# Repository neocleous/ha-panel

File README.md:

# HA Panel: design files

This branch, `docs`, holds the design of a Home Assistant touch panel: its custom circuit boards and its 3D-printed
enclosure. The panel's software is on the [`main`](https://github.com/neocleous/ha-panel/tree/main) branch.

## The panel
A free-standing Home Assistant panel. A Raspberry Pi 5 shows a full-screen dashboard on a Waveshare 8-inch DSI
touchscreen (1280 × 800, landscape). Around it:
- two speakers (Dayton Audio DMA45-4), driven by the main board's TAS5756M amplifier;
- two microphones for voice, through a ReSpeaker Lite;
- a presence radar (Hi-Link LD2410C);
- air and light sensors (BME680, VEML6030);
- four touch keys below the screen;
- power from a 20 V USB-C charger.

Home Assistant runs on a separate server; the panel is its display, sensor and voice client.

## State (2026-11-23)
- **The boards:** the main board (rev 3.3), the touch board (rev E), the mic strips (rev 3) and the two paste stencils.
  Their fab files are made.
- **The enclosure: the Fusion model is at version 79 and waits for its print re-check.** Versions 68 and 69 replaced the
  melted and glued joints by screws and two printed clamps. Versions 70 to 79 built the fixes that the audit of version 69
  decided, and added a 17th printed part, the radar's holder.
- **The print files are version 67's.** Until the re-check has run and they are made again, they are out of date for the
  shell, the door, the cap, the grommet and the hood, and they lack the two clamps. After versions 70 to 79 they are out
  of date for every printed part but the cradle of the USB-C inlet board, and they lack the radar's holder as well.
- **Next:** the print re-check and the new print files, then a fit trial printed in PLA, the black ABS set, the boards'
  assembly, the build and bring-up.
- **The first panel (v1)** is built and in use. `main` installs its software.

## Folder map
```
hardware/              the three boards and the paste stencil
  main-board/          rev 3.3: power, amplifier, sockets
  mic-strip/           rev 3: one microphone per strip, two strips per panel
  touch-board/         rev E: the four touch keys
  stencil/             the paste stencils: the main board; the touch board with the mic strips
  notes/               parts lists, DigiKey and JLC notes, Raspberry Pi settings
  rev-c/               the first panel's touch board
enclosure/             the housing
  model-v68/           the scripts that made versions 68 and 69 of the Fusion model from version 67
  model-v70/           the scripts that made versions 70 to 79 from version 69 (the audit's fixes)
  print-files/         the scripts that make the print files from the Fusion model
  HA Panel Final.step  the first panel's enclosure
```

Start with [`hardware/README.md`](hardware/README.md) for the boards and [`enclosure/README.md`](enclosure/README.md)
for the housing.

## Where things are that are not in this repo
- **The enclosure model:** Autodesk Fusion, document "HA Panel v5 - tapered", version 79 (work in progress).
- **The print files:** Bambu Studio projects made from version 67, kept on the Mac in
  `~/Documents/HA_panel_renders/print_files_v67/`. Five parts in them are out of date (see
  [`enclosure/README.md`](enclosure/README.md)).
- **The assembly instructions:** not in the repo yet; their final issue is still to come.

## The software
On [`main`](https://github.com/neocleous/ha-panel/tree/main): the installer, the kiosk set-up and the sensor daemon. The
panel pulls `main` every night.

## History
On 2026-11-19 this branch was cleaned up: earlier board revisions, superseded fab sets, the enclosure's build scripts and
audits, and the design's working notes were removed. The history keeps all of it. The tree as it stood
before: [commit 45a38e4](https://github.com/neocleous/ha-panel/tree/45a38e49d72cf125aab3f4aa91dd065b3bc4f7ee).

## Licence
PolyForm Noncommercial 1.0.0: see [`LICENSE.md`](LICENSE.md).

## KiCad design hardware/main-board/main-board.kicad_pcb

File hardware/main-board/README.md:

# Main board, rev 3.3

The panel's power and audio board. It sits behind the display on a printed carrier.

- It takes 20 V from the USB-C inlet board (Adafruit 5807, a HUSB238 PD sink) and protects it.
- It makes 5 V for the Raspberry Pi 5 and the radar, and 3.3 V for the sensors.
- It drives the two speakers with a TAS5756M amplifier.
- It carries the sockets for the touch board, the radar and the two sensor leads, and the wire pads for the Pi's signals.

**State (2026-11-21):** rev 3.3, fab files issued on 2026-11-21 after the pre-order review. From rev 3.2: PS1's row of
13 pins moved 3.0 toward +v to match Mean Well's side view (its body and box did not move; it is to be checked on the
module when it arrives, see "PS1" below); the touch socket J6 takes +3V3 ahead of F4; the via in one of U100's paste
windows is taken out; every silk line is 0.15 wide. The board has not been built or tested yet.

**Checks (KiCad 9.0.9, 2026-11-21):** schematic 0 errors, 0 warnings (`erc-report.txt`); board 0 errors, 0 open
connections, 0 differences to the schematic, 3 warnings: the footprints of J6, J2 and C6 differ from KiCad's library
copies, on purpose (`drc-report.txt`; C6's + mark is 0.1 smaller to clear L1's outline with the wider silk).

**PS1, to check on arrival:** measure on the module, from the pin row, how far its component side stands (Mean Well's
side view: 5.0, the module board's component face 9 from the case's component side and the pins 4 from that face).
About 5.0: rev 3.3 stands. About 8.3: the pin row belongs where rev 3.2 had it; revert commit `5db1985` and issue the
set again. Anything else: stop and look again before soldering.

## Files
| File | What |
|---|---|
| `main-board.kicad_pro`, `main-board.kicad_pcb`, five `.kicad_sch` | the design, KiCad 9.0.9. Project libraries: `lib/ha_panel.kicad_sym`, `lib/ha_panel.pretty` |
| `main-board-schematic.pdf` | the schematic, 5 pages |
| `main-board-rev3.3-assembly.pdf` | **the assembly drawing**, A3, 4 pages: all 120 part names; all values; the placing list with the maker's part numbers; the test pads, connectors and the back face. Previews of pages 1 and 2: `main-board-rev3.3-assembly-names.png`, `-values.png` |
| [`fab/`](fab/) | **what goes to JLC:** `main-board-rev3.3-jlc-2026-11-21.zip`, the same files unzipped in `gerbers/`, the hole list, the check of the set, and the order sheet; `superseded/` holds the rev 3.2 set, which must not be ordered |
| [`NOTES.md`](NOTES.md) | every value of the circuit with its source; the test pads; the layout |
| [`gpio-leads.md`](gpio-leads.md) | the 13 Pi signal wires: pad, Pi pin, housing, colour |
| `main-board-rev3.2.step`, `main-board-rev3.1-plug-envelopes.step`, [`MAIN_env.md`](MAIN_env.md) | for the enclosure model: the populated board, the plug envelopes, the outline, holes and heights. The STEP file is rev 3.2's: on rev 3.3 only PS1's 13 pin holes sit 3.0 further toward +v, and its pin ends behind the board are in `MAIN_env.md` §5. It was not exported again because this session had no KiCad 3D-model library |
| `main-board-copper-F-B.png` | both outer copper layers (rev 3.3) |
| `main-board-3d-door-side.png`, `main-board-3d-back.png` | renders of the populated board, rev 3.2: on rev 3.3 PS1's pins and its two legends sit 3.0 higher, and the back reads `REV 3.3 2026-11-21` |
| `erc-report.txt`, `drc-report.txt` | KiCad's schematic and board checks |
| [`tools/`](tools/) | scripts that export and check the fab set and the stencil, and draw the assembly drawing |

## How to order
- **Upload** `fab/main-board-rev3.3-jlc-2026-11-21.zip` to JLC as a bare board: no assembly, so no BOM or placement
  file. sha256 `26ff743470ad6834af4412218b2413478ce8ec22a962c775d0f4b1875617acdd`. It replaces the rev 3.2 zip.
- **Options in short:** 4 layers, 87.0 × 57.9 mm, FR-4, 1.6 mm, black with white silkscreen, ENIG, 1 oz outer and
  0.5 oz inner copper, stack-up JLC04161H-7628, vias plugged, outline tolerance ±0.2, "Remove Mark", 5 pieces (1 needed).
  Every option with its reason, and what JLC's review may ask: [`fab/ORDER-SHEET.md`](fab/ORDER-SHEET.md).
- **Paste stencil:** a separate line, 100 × 100 mm, for this board alone: [`../stencil/`](../stencil/).

## Parts
- Every part with its DigiKey line: [`../notes/bom-2026-11-17.md`](../notes/bom-2026-11-17.md), section "Main board
  rev 3.2" (rev 3.3 changed no part). The DigiKey quick-add list is [`../notes/digikey-bom.csv`](../notes/digikey-bom.csv).
- **One 0805 part reads 4.7 µF:** TDK C2012X7R1H475K125AC (50 V). It goes to all five places: C12, C101, C102, C122
  and C123.
- **Not from DigiKey:** LK1, a short piece of 1.0 mm tinned copper wire.

## The board in numbers
- **87.0 × 57.9 × 1.6 mm, 4 layers,** with a relief 1.5 deep in the side edge toward the left speaker (floor over
  v +1.5 … +13.0, inner corners r 1.0). Four 3.2 holes for M3 × 8 screws.
- **Layers:** door side parts and signals · layer 2 ground · layer 3 +5 V, +20 V and the amplifier's supply · back
  signals and ground. Stack-up JLC04161H-7628: copper 0.035 / 0.0152 / 0.0152 / 0.035, prepreg 0.2104, core 1.065.
- **120 names:** 72 surface-mount parts fitted and 9 not fitted, 13 through-hole parts, 3 blocks of wire pads
  (J3, J4, J7), 19 test pads, 4 holes. **Every part is on the door side; nothing is fitted on the back.**
- **Sizes:** nothing smaller than 0603; the finest pitches are U100 (0.5) and U1 (0.65). Connectors are through-hole.
- **Vias:** 243 — 87 of 0.2/0.45, 131 of 0.3/0.6, 25 of 0.4/0.8. Tracks 0.15 and wider. Copper to the edge 0.30;
  the pours 0.50 at the relief.
- **Frame used in every document:** seen from the door, u to the right (toward the left speaker), v up, origin in the
  middle of the board. "From the left edge" is u + 43.5; "from the bottom edge" is v + 28.95.

## Sheets
1. Root — index.
2. **20 V inlet and protection** — J1 (from the USB-C inlet board) → F1 5 A → TPS16630 (under-voltage 17.05 V,
   over-voltage 24.06 V, current limit 3.28 A, soft start 19.6 ms) → +20 V with D1 SMBJ22A.
3. **5 V supply and outputs** — 120 µF – L1 15 µH – 120 µF → NID100-5 (enabled by the protection chip's power-good) →
   22 µF + D2 SMBJ6.0A-E → Pi branch (F2 10 A → wire link LK1 → USB-C socket J2, 10 kΩ on each CC pin) and radar
   branch (F3 1 A). Trim network R8/R9 not fitted.
4. **3.3 V, Pi link, sensors, radar, echo tap** — TPS70933 (enabled by the Pi's 3.3 V) → sensor branch through F4
   (BME680 and VEML6030), the touch socket J6 straight from the regulator (since 2026-11-21) and the amplifier's logic
   rail; 13 wire pads for the Pi's signals (J3, J4); radar (J5) and touch (J6) sockets; one
   4-pin header each for the BME680 (J10) and the VEML6030 (J11); echo tap J7 with six links not fitted.
5. **Amplifier** — TAS5756M stereo, I²C address 0x4C, mute on GPIO22, 10 µH + 0.68 µF output filters, speaker sockets
   J8 (left) and J9 (right).

Every value's source: [`NOTES.md`](NOTES.md) §1 to §4.

## Default fit
| Option | Default | Alternative |
|---|---|---|
| Echo reference | **from USB:** R20–R25 not fitted, J7 empty | from I²S: fit R20–R23 (and R24/R25), other firmware |
| 5 V trim | R8, R9 not fitted (5.0 V) | R8 raises the output; value found on the bench at TP13 |
| Amplifier logic rail | R26 fitted (from the board's 3.3 V) | R27 instead of R26 (from the Pi's 3.3 V) |
| I²S series resistors | R14–R16 0 Ω | 22–47 Ω if the edges ring |
| 5 V module enable | R7 0 Ω (from power-good) | R7 open: the module runs whenever 20 V is there |
| Pi branch | LK1 fitted | LK1 open with a 10 A meter in its place (bench) |

## How to assemble
One pass on the hotplate for every surface-mount part, then the through-hole parts by iron. **Work from
`main-board-rev3.3-assembly.pdf`:** page 1 names, page 2 values, page 3 the placing list, page 4 the back.

**Before you start**
- **Paste:** Sn63/Pb37 no-clean (Chip Quik SMD291AXT4). Check its date.
- **Stencil:** the main board's own stencil, 100 × 100, 0.12 thick.
- **Four parts are moisture-sensitive.** Once its bag is open, each must be soldered within its floor life at 30 °C /
  60 % humidity or less; open the bags on the day. A part whose bag has been open longer is baked per J-STD-033 first.
  - U100 TAS5756M: level 3, 168 hours (TI's package information in the datasheet);
  - U1 TPS16630PWPT: level 2, 1 year (TI);
  - F4 Bel 0ZCJ0020FF2E: level 2a, 4 weeks (Bel, September 2025);
  - F5 Littelfuse 2920L260/33DR: level 2a, 4 weeks (Littelfuse, 2025-02-13).
- **Bare board, meter on ohms:** TP2 (20 V), pad 2 of F5 (amplifier supply), TP9 (5 V) and TP16 (3.3 V) each read open
  to TP7 (ground).

**Order**
1. **Paste** the door side through the stencil.
2. **Place the 72 surface-mount parts,** one line of the placing list at a time.
   - Leave nine places empty: R8, R9, R20 to R25, R27. Their pads get paste like the others.
   - D1 and D2: the band is the cathode and goes to pad 1 (red dot on the drawing).
   - U1, U2, U100: pin 1 at the red dot.
   - F1, F2 and F3 share one body: 5 A, 10 A and 1 A. Read the marking.
3. **Hotplate,** door side up. The back is bare, so the board lies flat. Profile below.
4. **Inspect** U100 and U1 under magnification for bridges and lifted pins, then every other joint.
5. **By iron: 13 through-hole parts,** fitted from the door side and soldered on the back, low to high:
   LK1 (tinned copper wire, 1.0 across) · J2 · J1, J8, J9, J5, J6 · J10, J11 · C7 · C5, C6 · PS1.
   - C5, C6, C7: the + lead in pad 1 (red dot). The stripe on the can marks the − lead.
   - PS1: pin 1 at the end the board marks "+Vo".
   - J2: its pin ends reach only 0.5 behind the board. Solder all 16 contacts and the 4 shell stakes.
   - **Cut the leads of C5, C6, C7 and LK1 to 1.5 or less behind the board.** In the unit the ReSpeaker and the
     display's power lead lie behind the board, and pin ends may stand out 4.0 at most there ([`MAIN_env.md`](MAIN_env.md) §5).
6. **The 13 Pi signal wires** (J3, J4): cut the terminal off the board end, push the wire in **from the back** and
   solder it **on the door side**. Pad by pad: [`gpio-leads.md`](gpio-leads.md). The back prints "PI 1-15" and "PI 35-40".
7. **J7 stays empty.**

**Hotplate profile**
- Follow the paste maker's profile. Chip Quik's chart for SMD291AX (datasheet rev 1.1) runs 25 → 100 → 150 °C, crosses
  the 183 °C melting point and tops at 235 °C, about 240 s in all.
- U100 is rated for 260 °C peak (TI), above that profile.
- U100's thermal pad: the stencil's 2 × 4 windows put 20.16 mm² of paste on it, 72.8 % of the package's nominal
  exposed pad and 61.9 % of the board's 3.70 × 8.80 opening; TI asks for 70 to 80 % (SLAS988B 11.1.3.2). Of the 39
  holes under the pad, 3 lie inside the opening and can take some solder; the other 36 are under soldermask.
- The flux is no-clean: nothing is washed.

**In the unit** (the panel's assembly instructions hold the steps): the display's power lead is plugged onto the
display before the board is screwed on. Plugging order on the board: speakers and 20 V, then touch and radar, then the
BME680 and the VEML6030, the Pi's power last.

## Test pads
19 bare round pads, 1.5 across, **on the door side**. No paste, no part. Distances in mm to the pad's centre, from the
board's left edge and from its bottom edge (the edge with the sockets), seen from the door. Map: page 4 of the drawing.

| Pad | Name | Net | From the left edge | From the bottom edge | What it is | Beside it |
|---|---|---|---|---|---|---|
| TP1 | VIN | VIN_EF | 22.5 | 10.3 | 20 V after the fuse F1, before the protection chip | left of R17; below D1 |
| TP2 | 20V | +20V | 31.1 | 19.6 | 20 V after the protection chip | above R5; left of R6 |
| TP3 | IMON | EF_IMON | 40.3 | 12.7 | current monitor, 0.279 V per A on the 20 V bus | right of R3; below J11 |
| TP4 | FLT | EF_FLT_N | 37.7 | 20.3 | protection chip fault (low = fault) | right of R6; above R4 |
| TP5 | PG | EF_PGOOD | 34.5 | 21.5 | power good (enables the 5 V module) | above R6; below PS1 |
| TP6 | SHDN | EF_SHDN | 40.8 | 20.4 | shutdown pin | above J11; below PS1 |
| TP7 | GND | GND | 42.3 | 9.2 | ground | right of C3; above J1 |
| TP8 | NID_IN | NID_VIN | 15.5 | 49.8 | 5 V module input, after the coil L1 | above C6; left of R21 |
| TP9 | 5V | +5V | 47.6 | 41.2 | 5 V module output | left of C7; right of C5 |
| TP10 | 5V_F | 5V_PI_F | 50.2 | 14.5 | 5 V after the Pi fuse F2 | right of J11; below LK1 |
| TP11 | EXT5V | VBUS_PI | 51.1 | 11.6 | 5 V at the Pi's USB-C socket | left of J6; above R16 |
| TP12 | RADAR | 5V_RADAR | 9.3 | 10.4 | radar 5 V, after its fuse F3 | below C10; left of J10 |
| TP13 | TRIM | NID_TRIM | 4.6 | 26.1 | 5 V module trim pin | left of PS1; below R7 |
| TP14 | RC | NID_RC | 4.6 | 32.5 | 5 V module on/off pin | left of PS1; above R7 |
| TP15 | GND | GND | 48.3 | 11.4 | ground | above R18; above R16 |
| TP16 | 3V3 | +3V3 | 27.2 | 21.2 | 3.3 V | right of C12; above D1 |
| TP17 | GND | GND | 21.4 | 14.6 | ground | left of D1; below U2 |
| TP19 | FAULT | AMP_FAULT_N | 67.5 | 52.5 | amplifier fault (low = fault) | above R26; above C119 |
| TP20 | GND | GND | 67.8 | 55.4 | ground | above R26; left of C118 |

- **There is no TP18.** The amplifier's supply is probed at **pad 2 of the fuse F5**, the pad nearer the right-hand
  edge (54.9 from the left edge, 53.3 from the bottom).
- **LK1** is the place for a meter in series with the Pi's 5 V (bench only).
- Seven test pads each have a via in them (TP2, TP7, TP9, TP15, TP17, TP19, TP20). No paste goes there, so they were
  left as they are. The via that lay inside one of the paste windows of U100's centre pad was taken out on 2026-11-21:
  its solder would have drained into the hole; the pad keeps its 39 thermal holes.

## Bring-up
On the bench, with the board out of the enclosure. A meter is enough. Ground: TP7, TP15, TP17 or TP20.

**Stage 1: 20 V only.** The USB-C inlet board and its charger on J1; no Pi, no leads, no sensors.

| Probe | Expect | Why |
|---|---|---|
| TP1, TP2, TP8, pad 2 of F5 | about 20 V, all equal | the protection chip is on above 17.05 V and off above 24.06 V (`NOTES.md` §1) |
| TP3 | 0.279 V per A of bus current: record it | `NOTES.md` §1 |
| TP6 | about 2.7 V | the pin's own open-circuit voltage (SLVSET9G 6.5) |
| TP9; TP10, TP11, TP12 | 4.90 to 5.10 V, all about equal | NID100-5, ± 2 % |
| TP13 | record it | 5 V trim (`NOTES.md` §2) |
| TP16, TP19, TP4 | about 0 V | the 3.3 V regulator waits for the Pi's 3.3 V on wire A1; both fault lines are pulled up to rails that are still off |

**Stage 2: Pi on.**
- Connect J2 to the Pi's USB-C; the three housings of the Pi signal wires (1 × 3 on pins 1-3-5, 2 × 5 on pins 7 to 16,
  2 × 3 on pins 35 to 40); the display's power lead on pins 2-4-6.
- Expect:

| Probe | Expect | Why |
|---|---|---|
| TP16 | 3.21 to 3.34 V | TPS70933-Q1: ± 1 % at 1 mA, plus up to 50 mV load and 10 mV line regulation (SLVSCE6D) |
| TP4, TP19 | about 3.3 V | no fault at the protection chip, none at the amplifier |
| `vcgencmd get_throttled` | `0x0` | the Pi's own under-voltage detector never tripped |
| TP11 and `vcgencmd pmic_read_adc EXT5V_V`, with the Pi under full load (all cores busy, display on) | 4.87 V or more | the upper tolerance of the Pi's under-voltage detector (4.63 V ± 5 %). If lower, R8 is found on the bench at TP13 (`NOTES.md` §2) before the panel goes into use |

**Stage 3: configuration and buses.** Apply [`../notes/pi-config.md`](../notes/pi-config.md), then plug the BME680
(J10), the VEML6030 (J11), the touch lead (J6) and the radar (J5).
- On 2026-11-21 the software on `main` did not yet carry all that `pi-config.md` plans. Still to come in the software
  step: the amplifier overlay `rpi-digiampplus,auto_mute_amp`, `dtparam=uart0=on`, `usb_max_current_enable=1`, the
  EEPROM's `PSU_MAX_CURRENT=5000`, and a driver for the LD2410C on `/dev/ttyAMA0`.
- **Start with everything plugged in:** switch the 20 V off and on with the Pi, the display, the radar and the sensors
  connected. TP9 must rise to 4.90–5.10 V once, without the module restarting, and the Pi must boot. Mean Well allows
  100 µF on the module's output; the board carries about 35 µF (`NOTES.md` §2), and the Pi's, the display's and the
  radar's own input capacitance is not published.
- `sudo i2cdetect -y 1`: **1b** (touch), **48** (VEML6030), **UU** at 4c (TAS5756M, held by its driver), and the
  BME680 at **76 or 77** (set by the sensor board's own strap).
- Radar: record TP12 with the LD2410C running and the Pi under full load. The LD2410C manual gives 5 to 12 V; the
  rail can sit just under 5 V (4.90 V at the module's lowest, less the drop to TP12). Expect no invalid frame at
  256000 8N1 on `/dev/ttyAMA0` at the lowest TP12 seen.
- Then the audio and voice tests on the bench.

## Earlier revisions
- **Rev 3.2 (fab issue of 2026-11-16):** its set is in `fab/superseded/` and must not be ordered: PS1's pin row did not
  match Mean Well's side view. Rev 3.3 also moved J6's supply ahead of F4, took out the via in U100's paste window and
  widened the silk; the paste did not change.
- **Rev 3.2 of 2026-11-14:** rev 3.1 with the relief in the side edge. The fab issue of 2026-11-16 changed copper and
  texts only: 39 vias moved out of pasted pads and 1 taken out, so that no hole can take a pad's solder on the hotplate;
  the pours kept 0.50 back from the relief (0.30 everywhere else); the stack-up JLC04161H-7628 written into the board
  file; the revision text on the back reads `REV 3.2 2026-11-16`. Outline, holes, heights and parts did not change.
- **Rev 3.1 (2026-11-11):** rev 3 with the top right hole moved, two headers moved, wider supply copper and ground
  pours on both outer layers.
- **Rev 3 (2026-11-11):** the board laid out again for its site behind the display, every part on the door side.
- **Rev 2.1 (2026-11-08):** the board for the earlier site, 90 × 55, with its own fab set of 2026-11-08, which is **not**
  for this board.

They are no longer in this folder. The history keeps each one with its reports and checks:
[`hardware/main-board/` before the clean-up (commit 45a38e4)](https://github.com/neocleous/ha-panel/tree/45a38e49d72cf125aab3f4aa91dd065b3bc4f7ee/hardware/main-board).

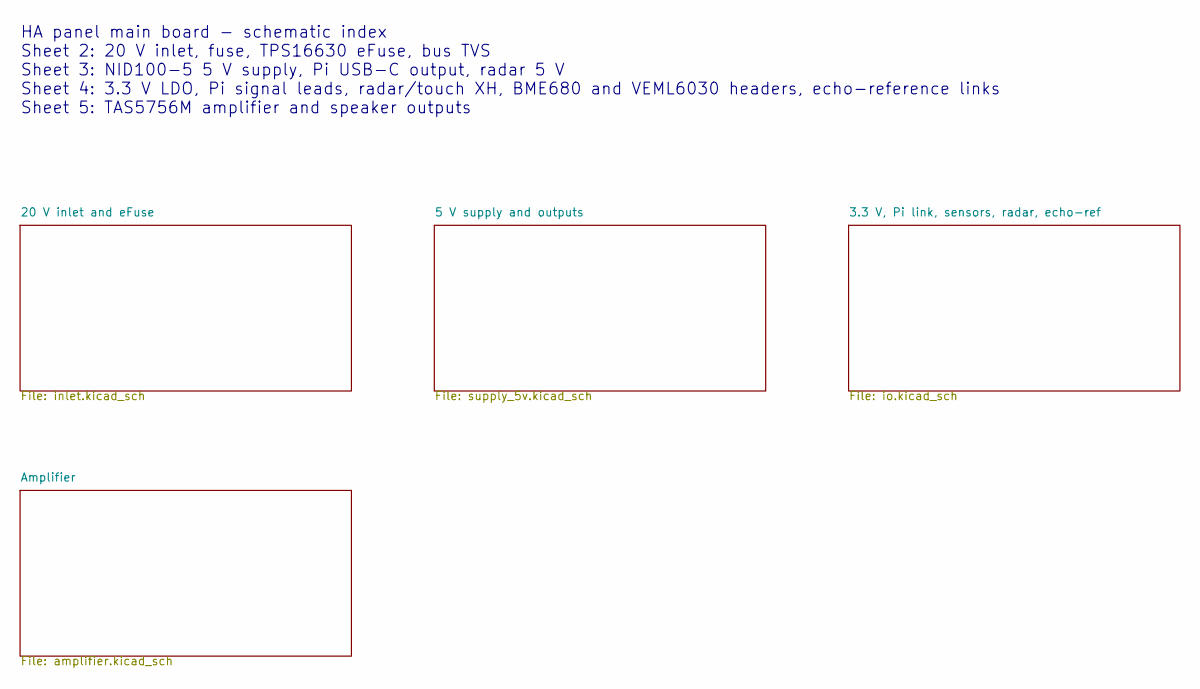
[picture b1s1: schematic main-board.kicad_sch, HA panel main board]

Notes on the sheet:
HA panel main board - schematic index Sheet 2: 20 V inlet, fuse, TPS16630 eFuse, bus TVS Sheet 3: NID100-5 5 V supply, Pi USB-C output, radar 5 V Sheet 4: 3.3 V LDO, Pi signal leads, radar/touch XH, BME680 and VEML6030 headers, echo-reference links Sheet 5: TAS5756M amplifier and speaker outputs

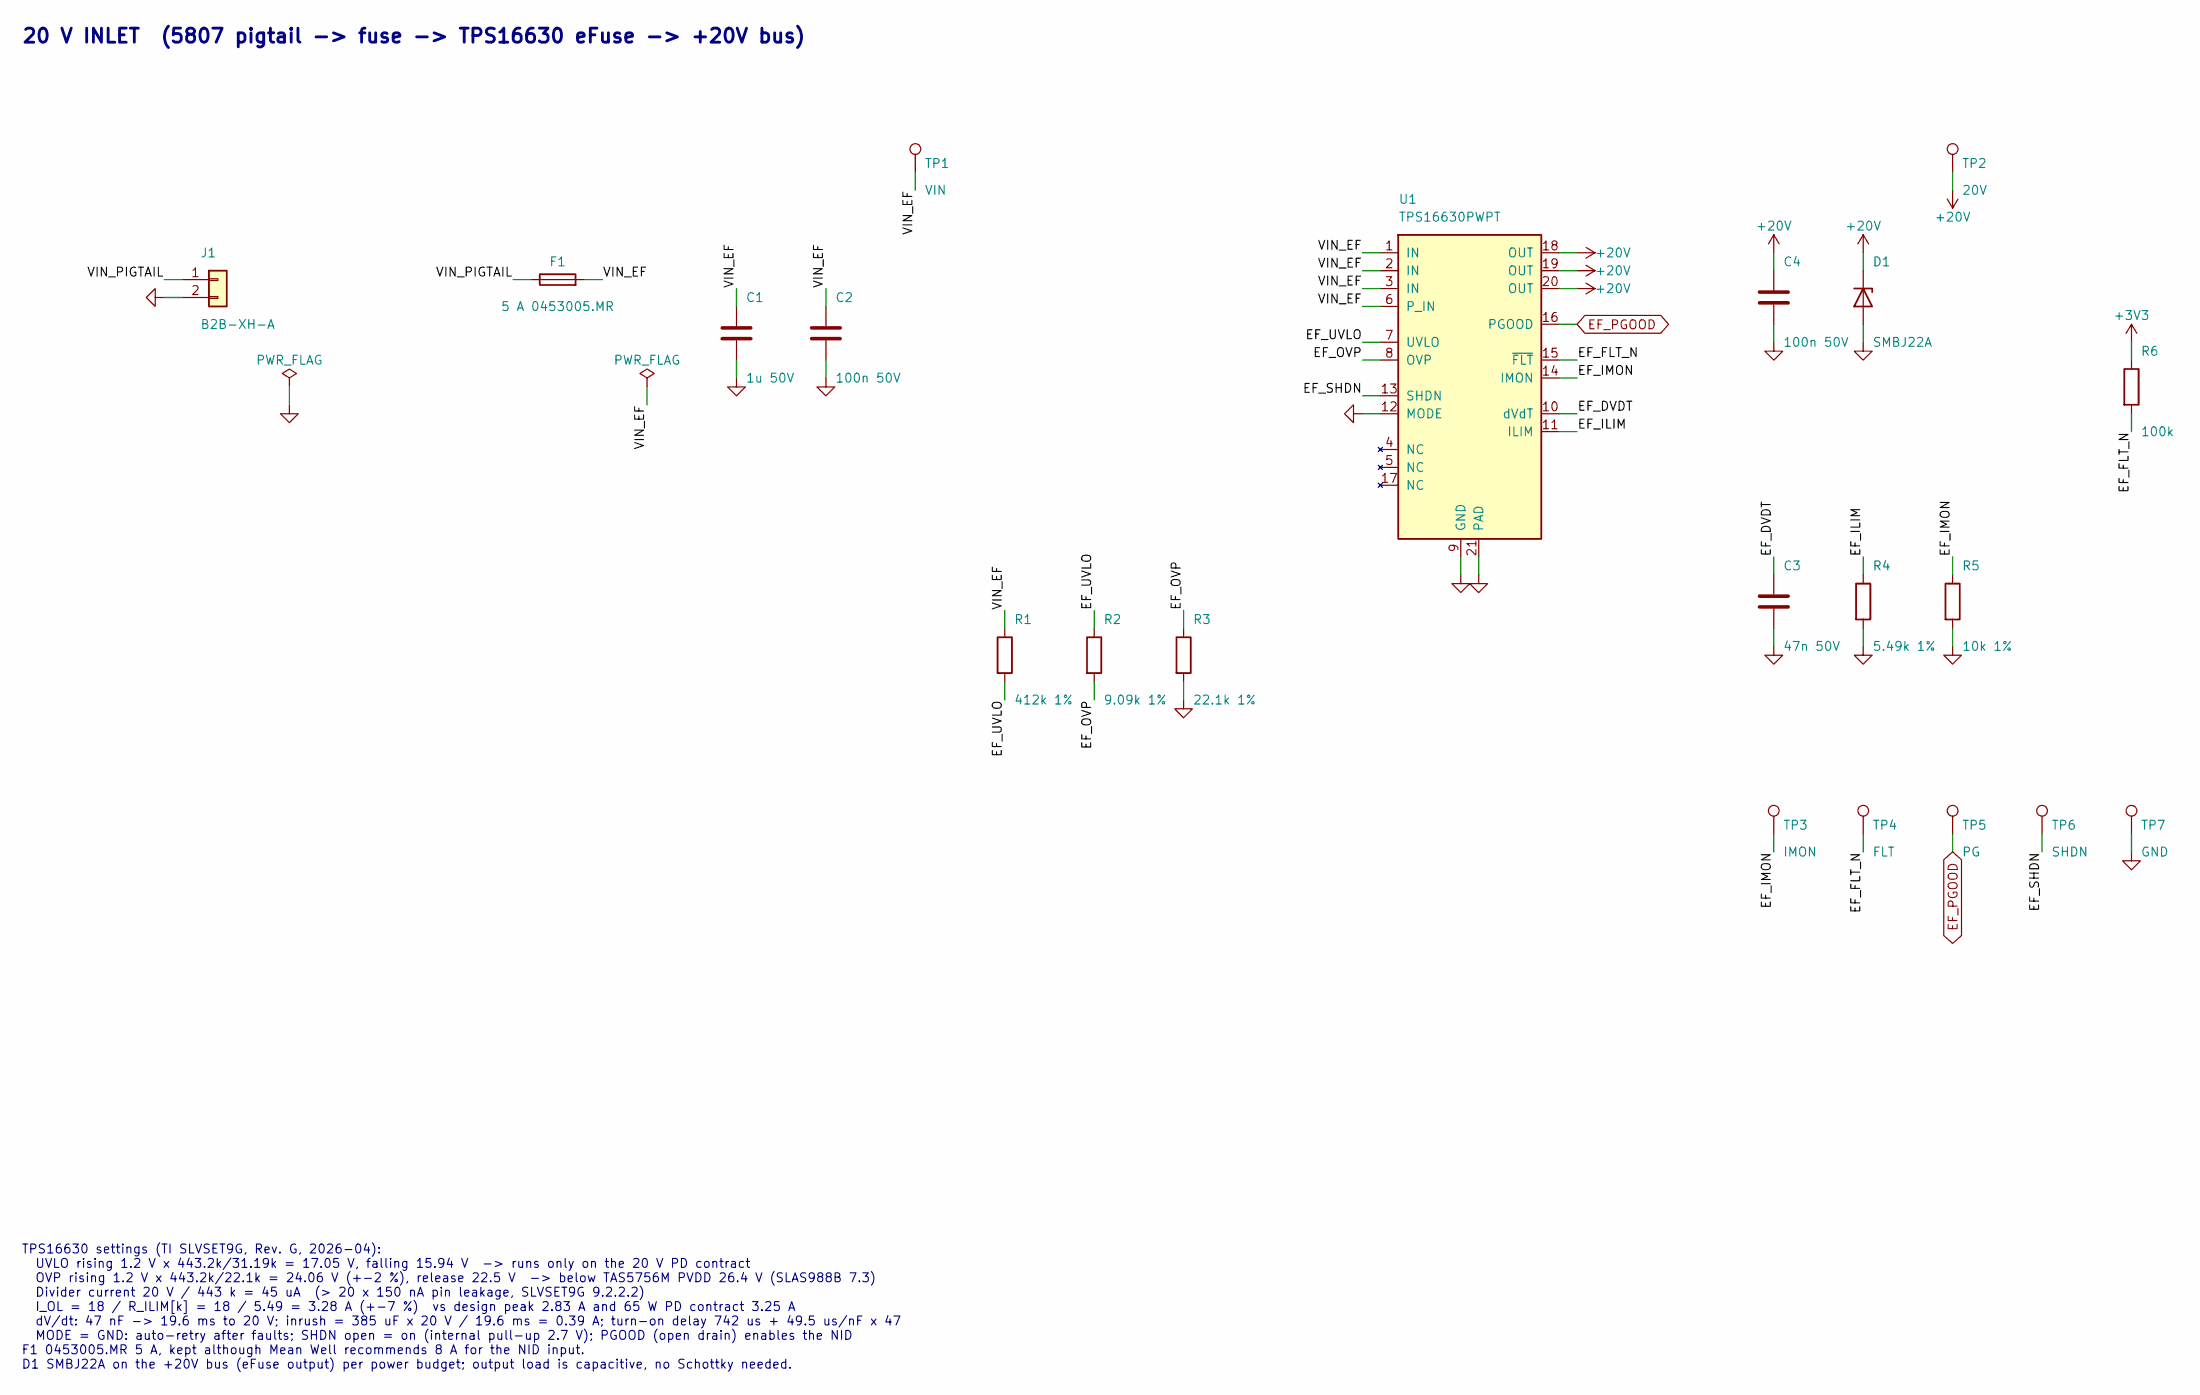
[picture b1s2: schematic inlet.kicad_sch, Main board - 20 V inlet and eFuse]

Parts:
C1: 1u 50V; C_0805_2012Metric; MPN 08055C105KAT2A; DigiKey 478-KGM21AR71H105KUCT-ND
C2, C4: 100n 50V; C_0603_1608Metric; MPN CC0603KRX7R9BB104; DigiKey 311-1344-1-ND
C3: 47n 50V; C_0603_1608Metric; MPN CL10B473KB8NNNC; DigiKey 1276-1063-1-ND
D1: SMBJ22A; D_SMB; MPN SMBJ22A; DigiKey SMBJ22ALFCT-ND
F1: 5 A 0453005.MR; Fuse_Littelfuse-NANO2-451_453; MPN 0453005.MR; DigiKey F3139CT-ND
J1: B2B-XH-A; JST_XH_B2B-XH-A_1x02_P2.50mm_Vertical; MPN B2B-XH-A; DigiKey 455-B2B-XH-A-ND
R1: 412k 1%; R_0603_1608Metric; MPN RC0603FR-07412KL; DigiKey 311-412KHRCT-ND
R2: 9.09k 1%; R_0603_1608Metric; MPN RC0603FR-079K09L; DigiKey 311-9.09KHRCT-ND
R3: 22.1k 1%; R_0603_1608Metric; MPN RC0603FR-0722K1L; DigiKey 311-22.1KHRCT-ND
R4: 5.49k 1%; R_0603_1608Metric; MPN RC0603FR-075K49L; DigiKey 311-5.49KHRCT-ND
R5: 10k 1%; R_0603_1608Metric; MPN RMCF0603FT10K0; DigiKey RMCF0603FT10K0CT-ND
R6: 100k; R_0603_1608Metric; MPN RMCF0603FT100K; DigiKey RMCF0603FT100KCT-ND
TP1: VIN; TestPoint_Pad_D1.5mm
TP2: 20V; TestPoint_Pad_D1.5mm
TP3: IMON; TestPoint_Pad_D1.5mm
TP4: FLT; TestPoint_Pad_D1.5mm
TP5: PG; TestPoint_Pad_D1.5mm
TP6: SHDN; TestPoint_Pad_D1.5mm
TP7: GND; TestPoint_Pad_D1.5mm
U1: TPS16630PWPT; HTSSOP-20-1EP_4.4x6.5mm_P0.65mm_EP3.4x6.5mm_Mask2.96x2.96mm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; MPN TPS16630PWPT; DigiKey 296-TPS16630PWPTCT-ND

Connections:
+3V3: R6.1; also elsewhere on the board
+20V: C4.1, D1.1 (K), TP2.1, U1.18 (OUT), U1.19 (OUT), U1.20 (OUT); also elsewhere on the board
/20 V inlet and eFuse/EF_DVDT: C3.1, U1.10 (dVdT)
/20 V inlet and eFuse/EF_FLT_N: R6.2, TP4.1, U1.15 (~FLT)
/20 V inlet and eFuse/EF_ILIM: R4.1, U1.11 (ILIM)
/20 V inlet and eFuse/EF_IMON: R5.1, TP3.1, U1.14 (IMON)
/20 V inlet and eFuse/EF_OVP: R2.2, R3.1, U1.8 (OVP)
/20 V inlet and eFuse/EF_SHDN: TP6.1, U1.13 (SHDN)
/20 V inlet and eFuse/EF_UVLO: R1.2, R2.1, U1.7 (UVLO)
/20 V inlet and eFuse/VIN_EF: C1.1, C2.1, F1.2, R1.1, TP1.1, U1.1 (IN), U1.2 (IN), U1.3 (IN), U1.6 (P_IN)
/20 V inlet and eFuse/VIN_PIGTAIL: F1.1, J1.1
EF_PGOOD: TP5.1, U1.16 (PGOOD); also elsewhere on the board
GND: C1.2, C2.2, C3.2, C4.2, D1.2 (A), J1.2, R3.2, R4.2, R5.2, TP7.1, U1.9 (GND), U1.12 (MODE), U1.21 (PAD); also elsewhere on the board

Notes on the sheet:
20 V INLET (5807 pigtail -> fuse -> TPS16630 eFuse -> +20V bus)
TPS16630 settings (TI SLVSET9G, Rev. G, 2026-04): UVLO rising 1.2 V x 443.2k/31.19k = 17.05 V, falling 15.94 V -> runs only on the 20 V PD contract OVP rising 1.2 V x 443.2k/22.1k = 24.06 V (+-2 %), release 22.5 V -> below TAS5756M PVDD 26.4 V (SLAS988B 7.3) Divider current 20 V / 443 k = 45 uA (> 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

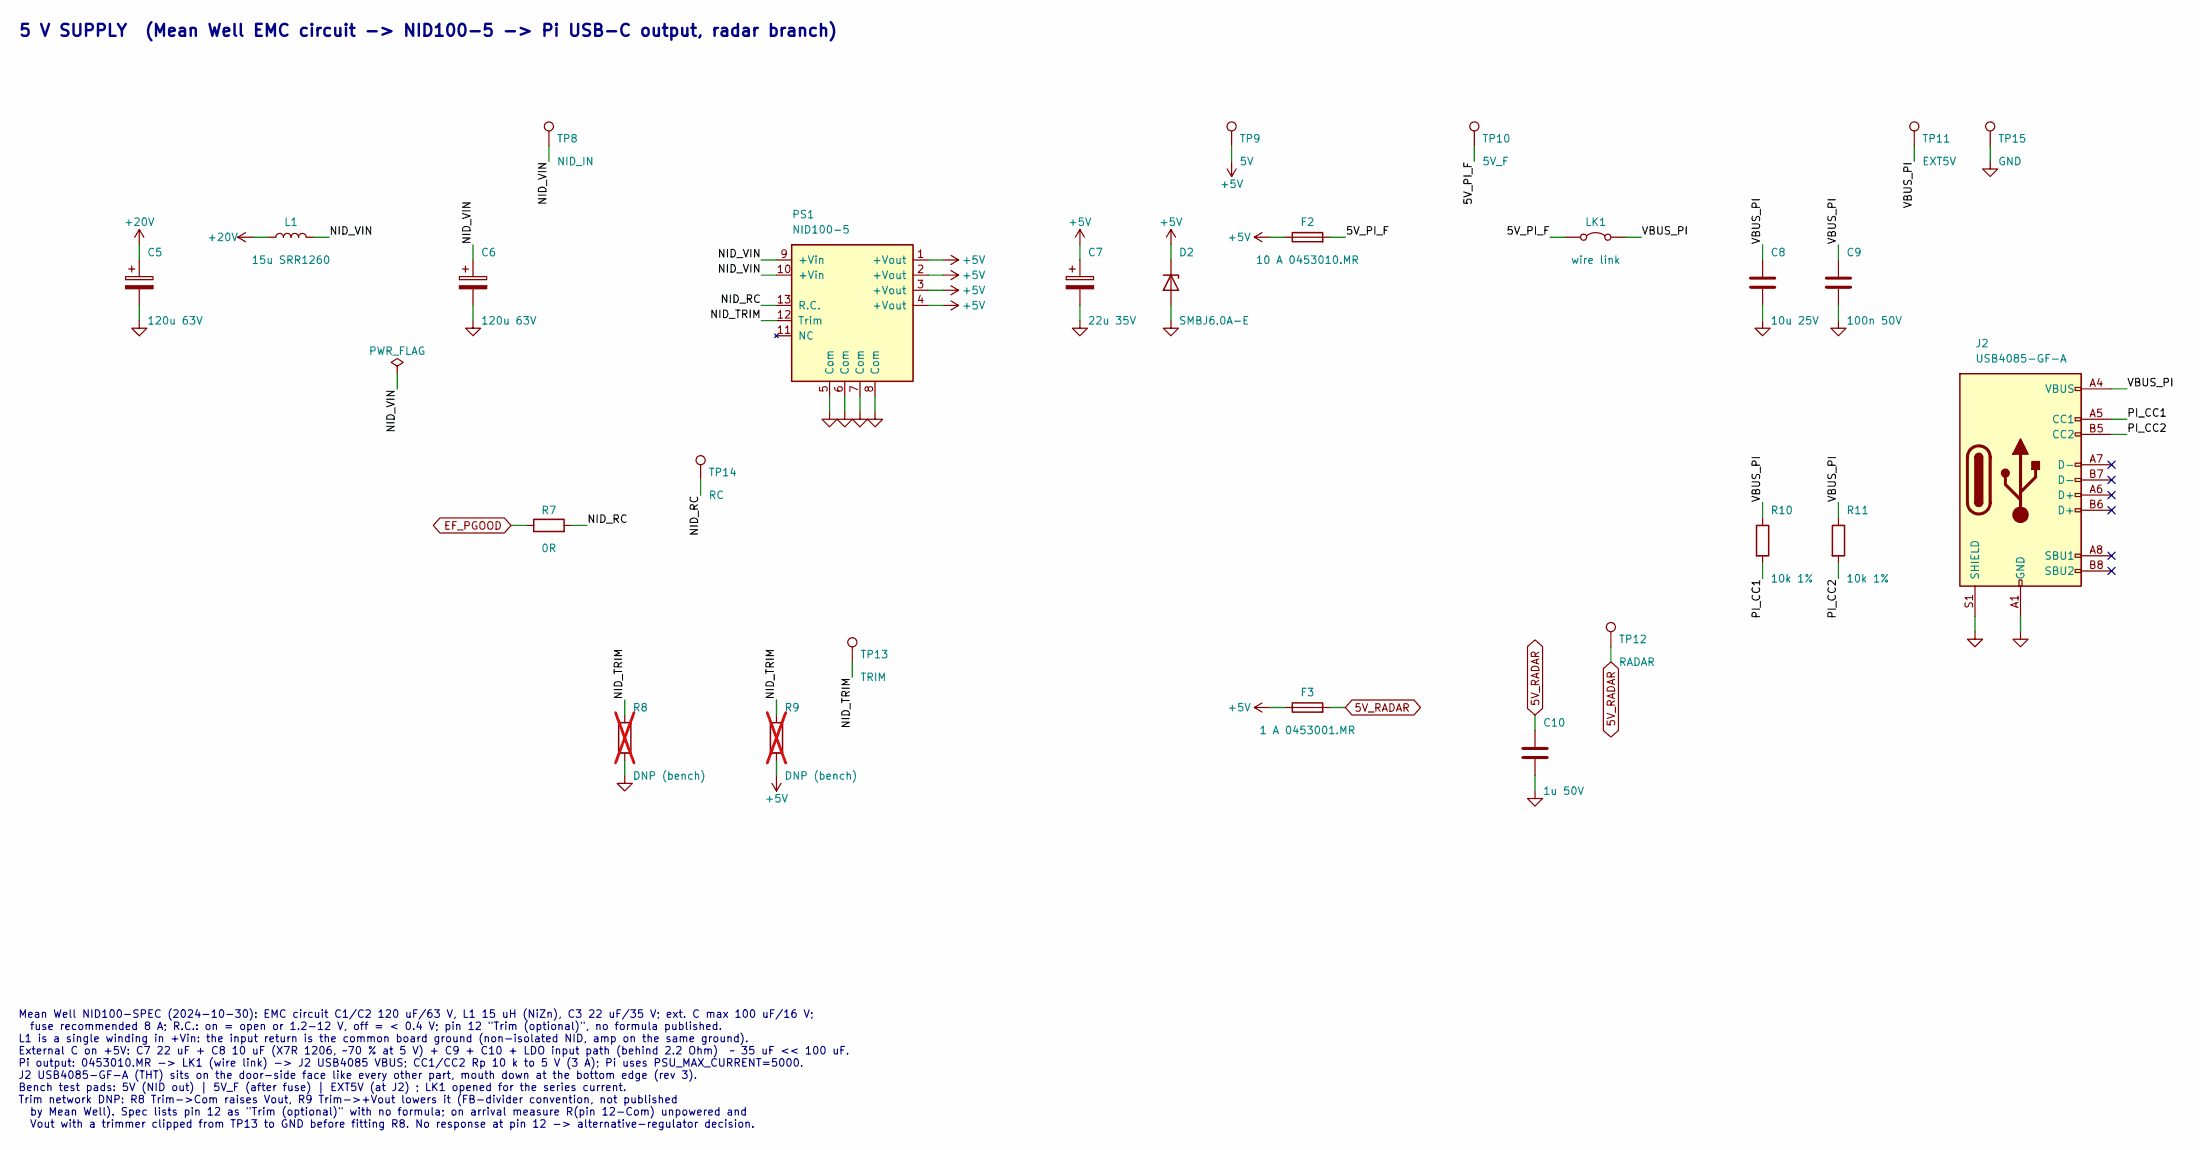
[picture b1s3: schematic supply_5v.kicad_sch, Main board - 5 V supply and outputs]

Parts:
C5, C6: 120u 63V; CP_Radial_D10.0mm_P5.00mm; MPN EEU-FR1J121B; DigiKey P15289CT-ND
C7: 22u 35V; CP_Radial_D5.0mm_P2.00mm; MPN 860160572003; DigiKey 732-9541-1-ND
C8: 10u 25V; C_1206_3216Metric; MPN C1206C106K4RACTU; DigiKey 399-C1206C106K4RACTUCT-ND
C9: 100n 50V; C_0603_1608Metric; MPN CC0603KRX7R9BB104; DigiKey 311-1344-1-ND
C10: 1u 50V; C_0805_2012Metric; MPN 08055C105KAT2A; DigiKey 478-KGM21AR71H105KUCT-ND
D2: SMBJ6.0A-E; D_SMB; MPN SMBJ6.0A-E; DigiKey 18-SMBJ6.0A-ECT-ND
F2: 10 A 0453010.MR; Fuse_Littelfuse-NANO2-451_453; MPN 0453010.MR; DigiKey F3141CT-ND
F3: 1 A 0453001.MR; Fuse_Littelfuse-NANO2-451_453; MPN 0453001.MR; DigiKey F3137CT-ND
J2: USB4085-GF-A; USB_C_Receptacle_GCT_USB4085; MPN USB4085-GF-A; DigiKey 2073-USB4085-GF-ACT-ND
L1: 15u SRR1260; L_Bourns_SRR1260; MPN SRR1260-150M; DigiKey SRR1260-150MCT-ND
LK1: wire link; WireLink_P7.62mm_D1.3mm
PS1: NID100-5; MeanWell_NID100_SIP-13; MPN NID100-5; DigiKey 1866-NID100-5-ND
R7: 0R; R_0603_1608Metric; MPN RC0603JR-070RL; DigiKey 311-0.0GRCT-ND
R8, R9: DNP (bench); R_0805_2012Metric; not fitted
R10, R11: 10k 1%; R_0603_1608Metric; MPN RMCF0603FT10K0; DigiKey RMCF0603FT10K0CT-ND
TP8: NID_IN; TestPoint_Pad_D1.5mm
TP9: 5V; TestPoint_Pad_D1.5mm
TP10: 5V_F; TestPoint_Pad_D1.5mm
TP11: EXT5V; TestPoint_Pad_D1.5mm
TP12: RADAR; TestPoint_Pad_D1.5mm
TP13: TRIM; TestPoint_Pad_D1.5mm
TP14: RC; TestPoint_Pad_D1.5mm
TP15: GND; TestPoint_Pad_D1.5mm

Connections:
5V_RADAR: C10.1, F3.2, TP12.1; also elsewhere on the board
+5V: C7.1, D2.1 (K), F2.1, F3.1, PS1.1 (+Vout), PS1.2 (+Vout), PS1.3 (+Vout), PS1.4 (+Vout), R9.2, TP9.1; also elsewhere on the board
+20V: C5.1, L1.1; also elsewhere on the board
/5 V supply and outputs/5V_PI_F: F2.2, LK1.1 (A), TP10.1
/5 V supply and outputs/NID_RC: PS1.13 (R.C.), R7.2, TP14.1
/5 V supply and outputs/NID_TRIM: PS1.12 (Trim), R8.1, R9.1, TP13.1
/5 V supply and outputs/NID_VIN: C6.1, L1.2, PS1.9 (+Vin), PS1.10 (+Vin), TP8.1
/5 V supply and outputs/PI_CC1: J2.A5 (CC1), R10.2
/5 V supply and outputs/PI_CC2: J2.B5 (CC2), R11.2
/5 V supply and outputs/VBUS_PI: C8.1, C9.1, J2.A4 (VBUS), J2.A9 (VBUS), J2.B4 (VBUS), J2.B9 (VBUS), LK1.2 (B), R10.1, R11.1, TP11.1
EF_PGOOD: R7.1; also elsewhere on the board
GND: C5.2, C6.2, C7.2, C8.2, C9.2, C10.2, D2.2 (A), J2.A1 (GND), J2.A12 (GND), J2.B1 (GND), J2.B12 (GND), J2.S1 (SHIELD), PS1.5 (Com), PS1.6 (Com), PS1.7 (Com), PS1.8 (Com), R8.2, TP15.1; also elsewhere on the board

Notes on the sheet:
5 V SUPPLY (Mean Well EMC circuit -> NID100-5 -> Pi USB-C output, radar branch)
Mean Well NID100-SPEC (2024-10-30): EMC circuit C1/C2 120 uF/63 V, L1 15 uH (NiZn), C3 22 uF/35 V; ext. C max 100 uF/16 V; fuse recommended 8 A; R.C.: on = open or 1.2-12 V, off = < 0.4 V; pin 12 "Trim (optional)", no formula published. L1 is a single winding in +Vin: the input return is the common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

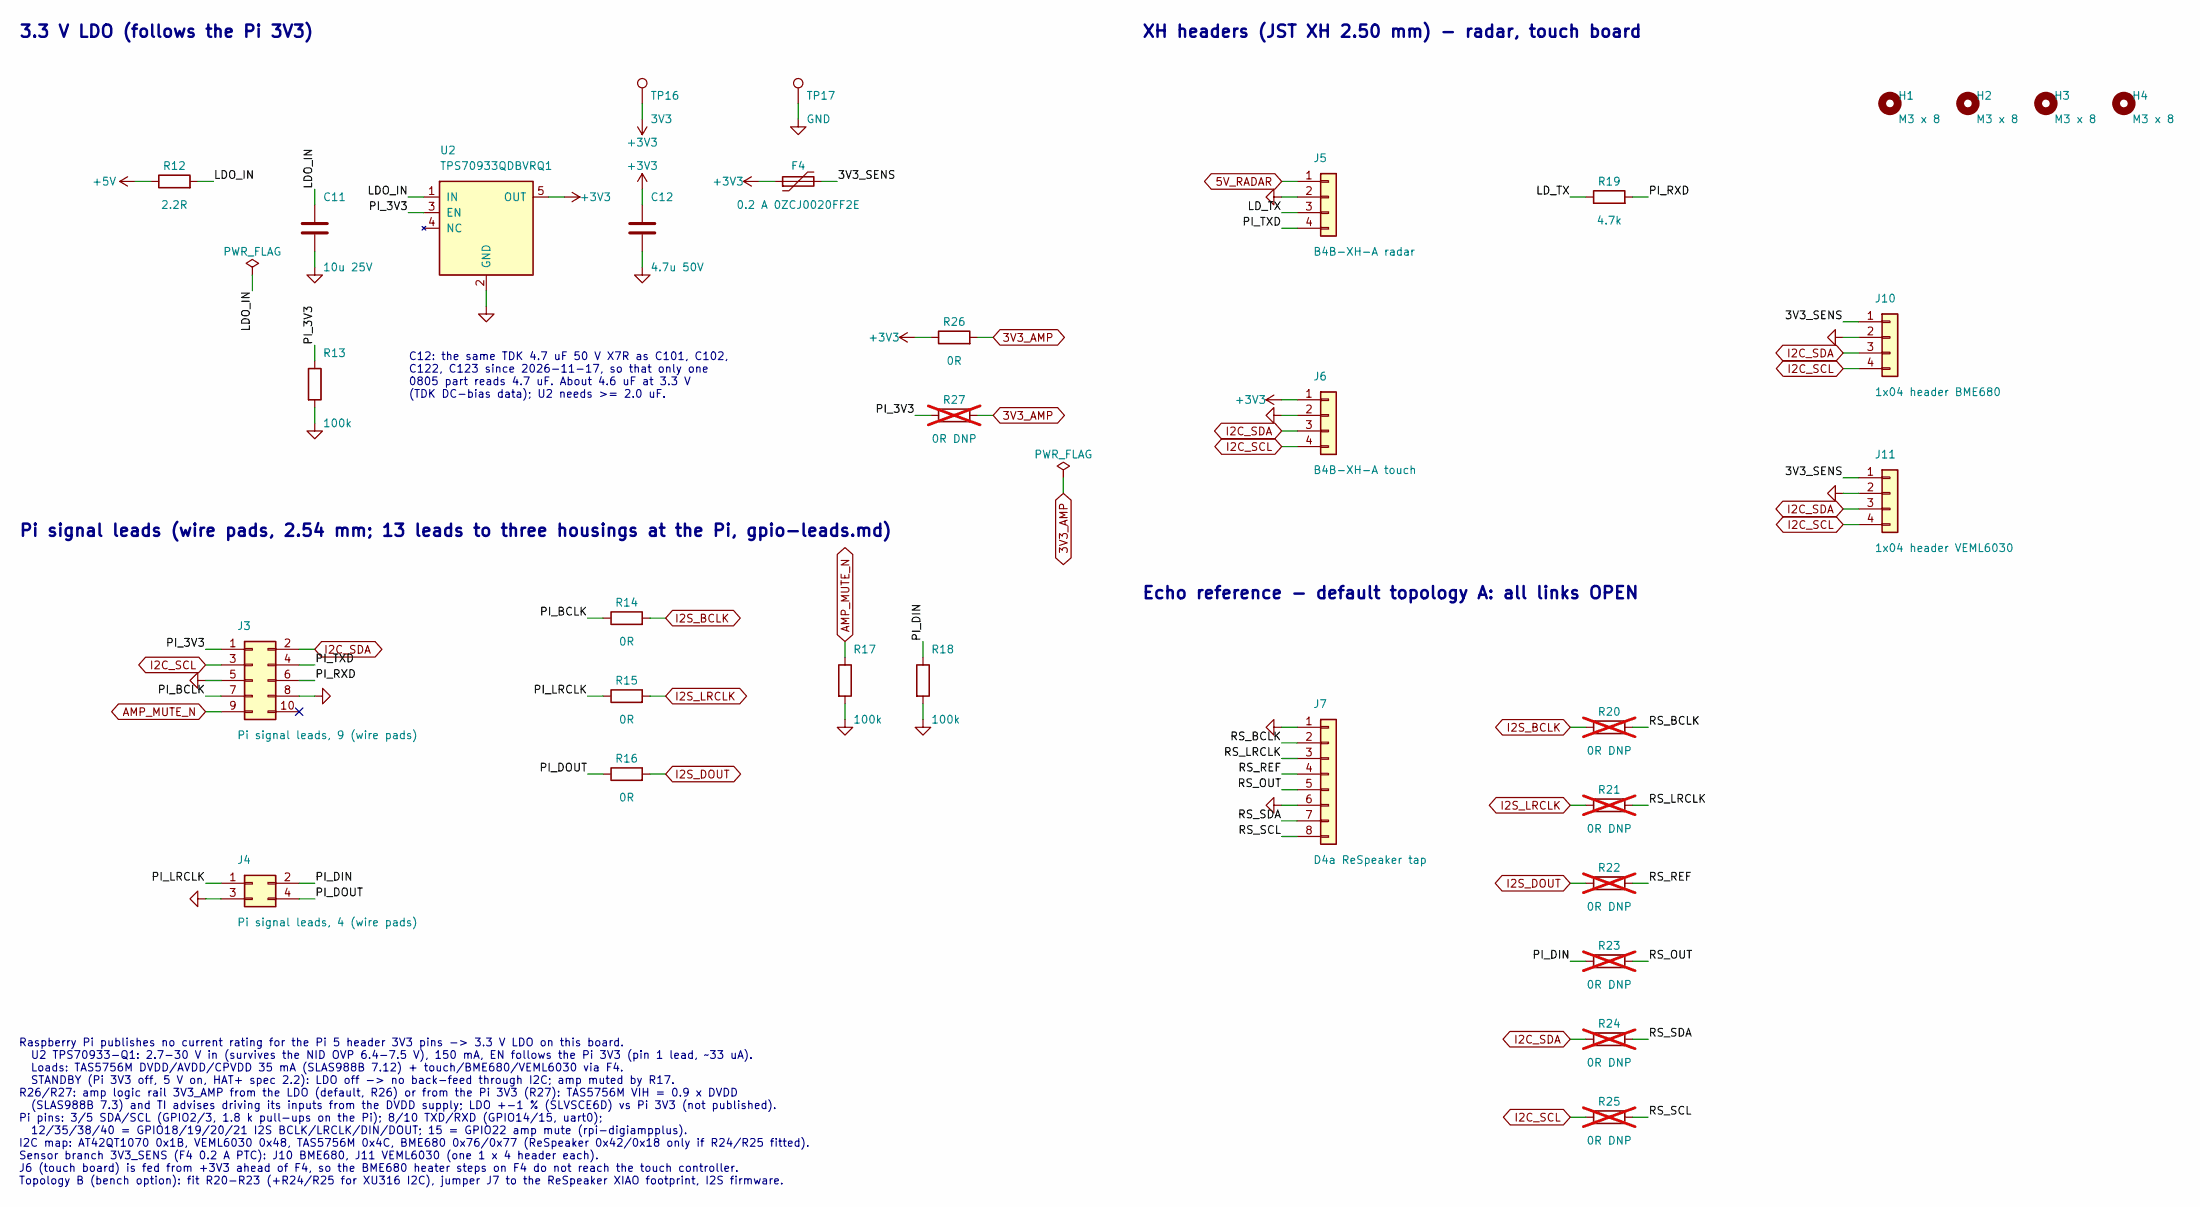
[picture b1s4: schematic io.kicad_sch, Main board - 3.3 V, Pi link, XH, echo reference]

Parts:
C11: 10u 25V; C_1206_3216Metric; MPN C1206C106K4RACTU; DigiKey 399-C1206C106K4RACTUCT-ND
C12: 4.7u 50V; C_0805_2012Metric; MPN C2012X7R1H475K125AC; DigiKey 445-C2012X7R1H475K125ACCT-ND
F4: 0.2 A 0ZCJ0020FF2E; Fuse_1206_3216Metric; MPN 0ZCJ0020FF2E; DigiKey 5923-0ZCJ0020FF2ECT-ND
H1, H2, H3, H4: M3 x 8; MountingHole_3.2mm_M3_Post
J3: Pi signal leads, 9 (wire pads); WirePads_2x05_P2.54mm_D1.0mm
J4: Pi signal leads, 4 (wire pads); WirePads_2x02_P2.54mm_D1.0mm
J5: B4B-XH-A radar; JST_XH_B4B-XH-A_1x04_P2.50mm_Vertical; MPN B4B-XH-A; DigiKey 455-B4B-XH-A-ND
J6: B4B-XH-A touch; JST_XH_B4B-XH-A_1x04_P2.50mm_Vertical; MPN B4B-XH-A; DigiKey 455-B4B-XH-A-ND
J7: D4a ReSpeaker tap; WirePads_1x08_P2.54mm_D1.0mm
J10: 1x04 header BME680; PinHeader_1x04_P2.54mm_Vertical; MPN PRPC004SAAN-RC; DigiKey 35-PRPC004SAAN-RC-ND
J11: 1x04 header VEML6030; PinHeader_1x04_P2.54mm_Vertical; MPN PRPC004SAAN-RC; DigiKey 35-PRPC004SAAN-RC-ND
R12: 2.2R; R_0805_2012Metric; MPN RMCF0805FT2R20; DigiKey RMCF0805FT2R20CT-ND
R13, R17, R18: 100k; R_0603_1608Metric; MPN RMCF0603FT100K; DigiKey RMCF0603FT100KCT-ND
R14, R15, R16, R26: 0R; R_0603_1608Metric; MPN RC0603JR-070RL; DigiKey 311-0.0GRCT-ND
R19: 4.7k; R_0603_1608Metric; MPN RC0603FR-074K7L; DigiKey 311-4.70KHRCT-ND
R20, R21, R22, R23, R24, R25, R27: 0R DNP; R_0603_1608Metric; MPN RC0603JR-070RL; DigiKey 311-0.0GRCT-ND; not fitted
TP16: 3V3; TestPoint_Pad_D1.5mm
TP17: GND; TestPoint_Pad_D1.5mm
U2: TPS70933QDBVRQ1; SOT-23-5; MPN TPS70933QDBVRQ1; DigiKey 296-40931-1-ND

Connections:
3V3_AMP: R26.2, R27.2; also elsewhere on the board
5V_RADAR: J5.1; also elsewhere on the board
+3V3: C12.1, F4.1, J6.1, R26.1, TP16.1, U2.5 (OUT); also elsewhere on the board
+5V: R12.1; also elsewhere on the board
/3.3 V, Pi link, sensors, radar, echo-ref/3V3_SENS: F4.2, J10.1, J11.1
/3.3 V, Pi link, sensors, radar, echo-ref/LDO_IN: C11.1, R12.2, U2.1 (IN)
/3.3 V, Pi link, sensors, radar, echo-ref/LD_TX: J5.3, R19.1
/3.3 V, Pi link, sensors, radar, echo-ref/PI_3V3: J3.1, R13.1, R27.1, U2.3 (EN)
/3.3 V, Pi link, sensors, radar, echo-ref/PI_BCLK: J3.7, R14.1
/3.3 V, Pi link, sensors, radar, echo-ref/PI_DIN: J4.2, R18.1, R23.1
/3.3 V, Pi link, sensors, radar, echo-ref/PI_DOUT: J4.4, R16.1
/3.3 V, Pi link, sensors, radar, echo-ref/PI_LRCLK: J4.1, R15.1
/3.3 V, Pi link, sensors, radar, echo-ref/PI_RXD: J3.6, R19.2
/3.3 V, Pi link, sensors, radar, echo-ref/PI_TXD: J3.4, J5.4
/3.3 V, Pi link, sensors, radar, echo-ref/RS_BCLK: J7.2, R20.2
/3.3 V, Pi link, sensors, radar, echo-ref/RS_LRCLK: J7.3, R21.2
/3.3 V, Pi link, sensors, radar, echo-ref/RS_OUT: J7.5, R23.2
/3.3 V, Pi link, sensors, radar, echo-ref/RS_REF: J7.4, R22.2
/3.3 V, Pi link, sensors, radar, echo-ref/RS_SCL: J7.8, R25.2
/3.3 V, Pi link, sensors, radar, echo-ref/RS_SDA: J7.7, R24.2
AMP_MUTE_N: J3.9, R17.1; also elsewhere on the board
GND: C11.2, C12.2, J3.5, J3.8, J4.3, J5.2, J6.2, J7.1, J7.6, J10.2, J11.2, R13.2, R17.2, R18.2, TP17.1, U2.2 (GND); also elsewhere on the board
I2C_SCL: J3.3, J6.4, J10.4, J11.4, R25.1; also elsewhere on the board
I2C_SDA: J3.2, J6.3, J10.3, J11.3, R24.1; also elsewhere on the board
I2S_BCLK: R14.2, R20.1; also elsewhere on the board
I2S_DOUT: R16.2, R22.1; also elsewhere on the board
I2S_LRCLK: R15.2, R21.1; also elsewhere on the board

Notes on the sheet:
3.3 V LDO (follows the Pi 3V3)
C12: the same TDK 4.7 uF 50 V X7R as C101, C102, C122, C123 since 2026-11-17, so that only one 0805 part reads 4.7 uF. About 4.6 uF at 3.3 V (TDK DC-bias data); U2 needs >= 2.0 uF.
Pi signal leads (wire pads, 2.54 mm; 13 leads to three housings at the Pi, gpio-leads.md)
XH headers (JST XH 2.50 mm) - radar, touch board
Echo reference - default topology A: all links OPEN
Raspberry Pi publishes no current rating for the Pi 5 header 3V3 pins -> 3.3 V LDO on this board. U2 TPS70933-Q1: 2.7-30 V in (survives the NID OVP 6.4-7.5 V), 150 mA, EN follows the Pi 3V3 (pin 1 lead, ~33 uA). Loads: TAS5756M DVDD/AVDD/CPVDD 35 mA (SLAS988B 7.12) + touch/BME680/VEML6030 via F4. S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
